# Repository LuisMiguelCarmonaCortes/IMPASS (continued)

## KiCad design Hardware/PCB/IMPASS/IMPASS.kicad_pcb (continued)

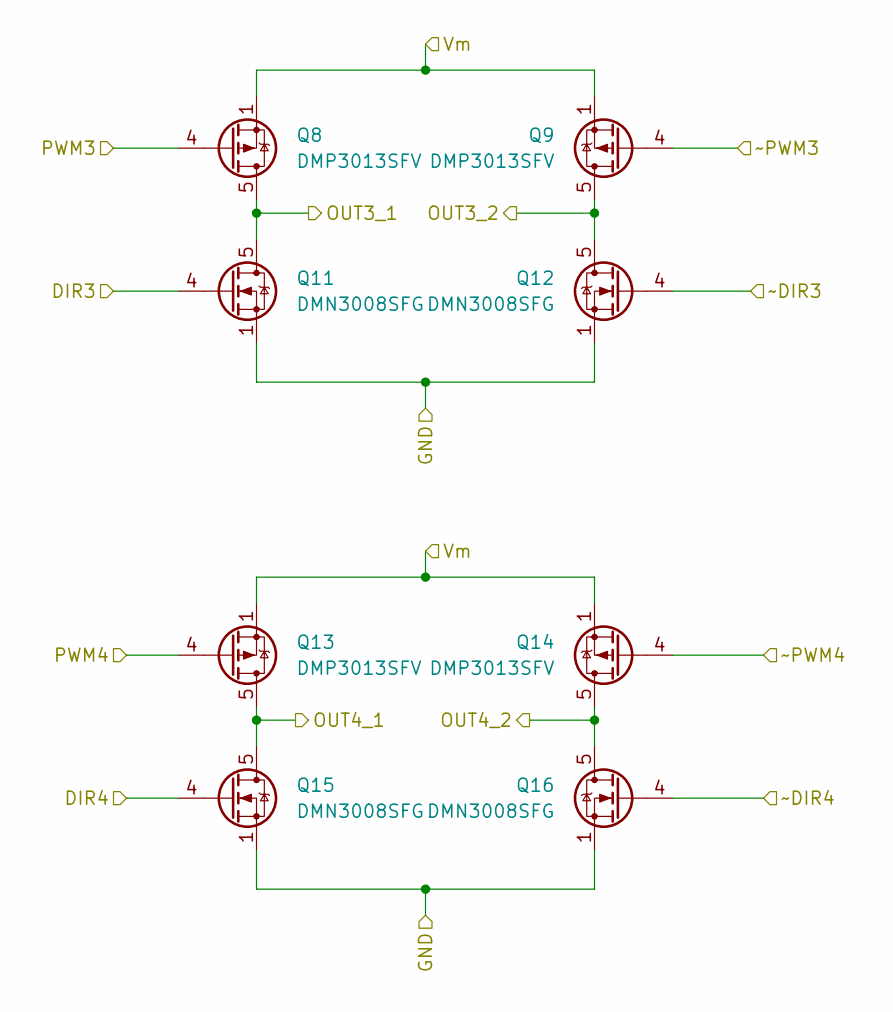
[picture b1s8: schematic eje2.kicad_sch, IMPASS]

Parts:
Q8, Q9, Q13, Q14: DMP3013SFV; Diodes_PowerDI3333-8
Q11, Q12, Q15, Q16: DMN3008SFG; Diodes_PowerDI3333-8

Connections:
12v: Q8.1 (S), Q8.2 (S), Q8.3 (S), Q9.1 (S), Q9.2 (S), Q9.3 (S), Q13.1 (S), Q13.2 (S), Q13.3 (S), Q14.1 (S), Q14.2 (S), Q14.3 (S); also elsewhere on the board
/Placa_potencia/Eje2/DIR3: Q11.4 (G); also elsewhere on the board
/Placa_potencia/Eje2/DIR4: Q15.4 (G); also elsewhere on the board
/Placa_potencia/Eje2/OUT3_1: Q8.5 (D), Q11.5 (D); also elsewhere on the board
/Placa_potencia/Eje2/OUT3_2: Q9.5 (D), Q12.5 (D); also elsewhere on the board
/Placa_potencia/Eje2/OUT4_1: Q13.5 (D), Q15.5 (D); also elsewhere on the board
/Placa_potencia/Eje2/OUT4_2: Q14.5 (D), Q16.5 (D); also elsewhere on the board
/Placa_potencia/Eje2/PWM3: Q8.4 (G); also elsewhere on the board
/Placa_potencia/Eje2/PWM4: Q13.4 (G); also elsewhere on the board
/Placa_potencia/Eje2/~DIR3: Q12.4 (G); also elsewhere on the board
/Placa_potencia/Eje2/~DIR4: Q16.4 (G); also elsewhere on the board
/Placa_potencia/Eje2/~PWM3: Q9.4 (G); also elsewhere on the board
/Placa_potencia/Eje2/~PWM4: Q14.4 (G); also elsewhere on the board
GND1: Q11.1 (S), Q11.2 (S), Q11.3 (S), Q12.1 (S), Q12.2 (S), Q12.3 (S), Q15.1 (S), Q15.2 (S), Q15.3 (S), Q16.1 (S), Q16.2 (S), Q16.3 (S); also elsewhere on the board

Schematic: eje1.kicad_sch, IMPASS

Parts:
Q2, Q3, Q4, Q6: DMP3013SFV; Diodes_PowerDI3333-8
Q71, Q73, Q75, Q77: DMN3008SFG; Diodes_PowerDI3333-8

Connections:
12v: Q2.1 (S), Q2.2 (S), Q2.3 (S), Q3.1 (S), Q3.2 (S), Q3.3 (S), Q4.1 (S), Q4.2 (S), Q4.3 (S), Q6.1 (S), Q6.2 (S), Q6.3 (S); also elsewhere on the board
/Placa_potencia/Eje1/DIR1: Q71.4 (G); also elsewhere on the board
/Placa_potencia/Eje1/DIR2: Q73.4 (G); also elsewhere on the board
/Placa_potencia/Eje1/OUT1_1: Q2.5 (D), Q71.5 (D); also elsewhere on the board
/Placa_potencia/Eje1/OUT1_2: Q3.5 (D), Q75.5 (D); also elsewhere on the board
/Placa_potencia/Eje1/OUT2_1: Q4.5 (D), Q73.5 (D); also elsewhere on the board
/Placa_potencia/Eje1/OUT2_2: Q6.5 (D), Q77.5 (D); also elsewhere on the board
/Placa_potencia/Eje1/PWM1: Q2.4 (G); also elsewhere on the board
/Placa_potencia/Eje1/PWM2: Q4.4 (G); also elsewhere on the board
/Placa_potencia/Eje1/~DIR1: Q75.4 (G); also elsewhere on the board
/Placa_potencia/Eje1/~DIR2: Q77.4 (G); also elsewhere on the board
/Placa_potencia/Eje1/~PWM1: Q3.4 (G); also elsewhere on the board
/Placa_potencia/Eje1/~PWM2: Q6.4 (G); also elsewhere on the board
GND1: Q71.1 (S), Q71.2 (S), Q71.3 (S), Q73.1 (S), Q73.2 (S), Q73.3 (S), Q75.1 (S), Q75.2 (S), Q75.3 (S), Q77.1 (S), Q77.2 (S), Q77.3 (S); also elsewhere on the board

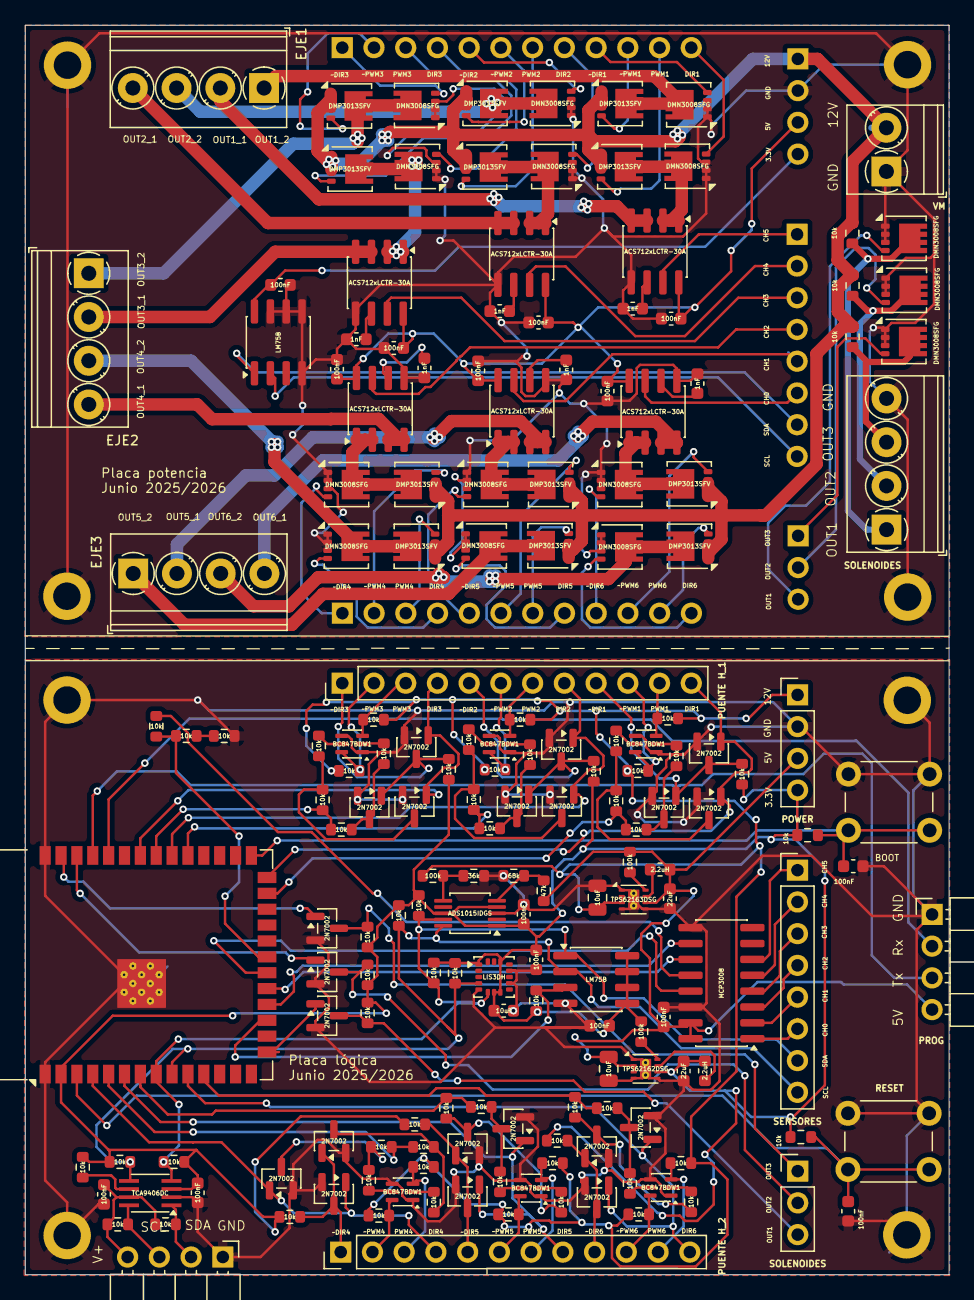
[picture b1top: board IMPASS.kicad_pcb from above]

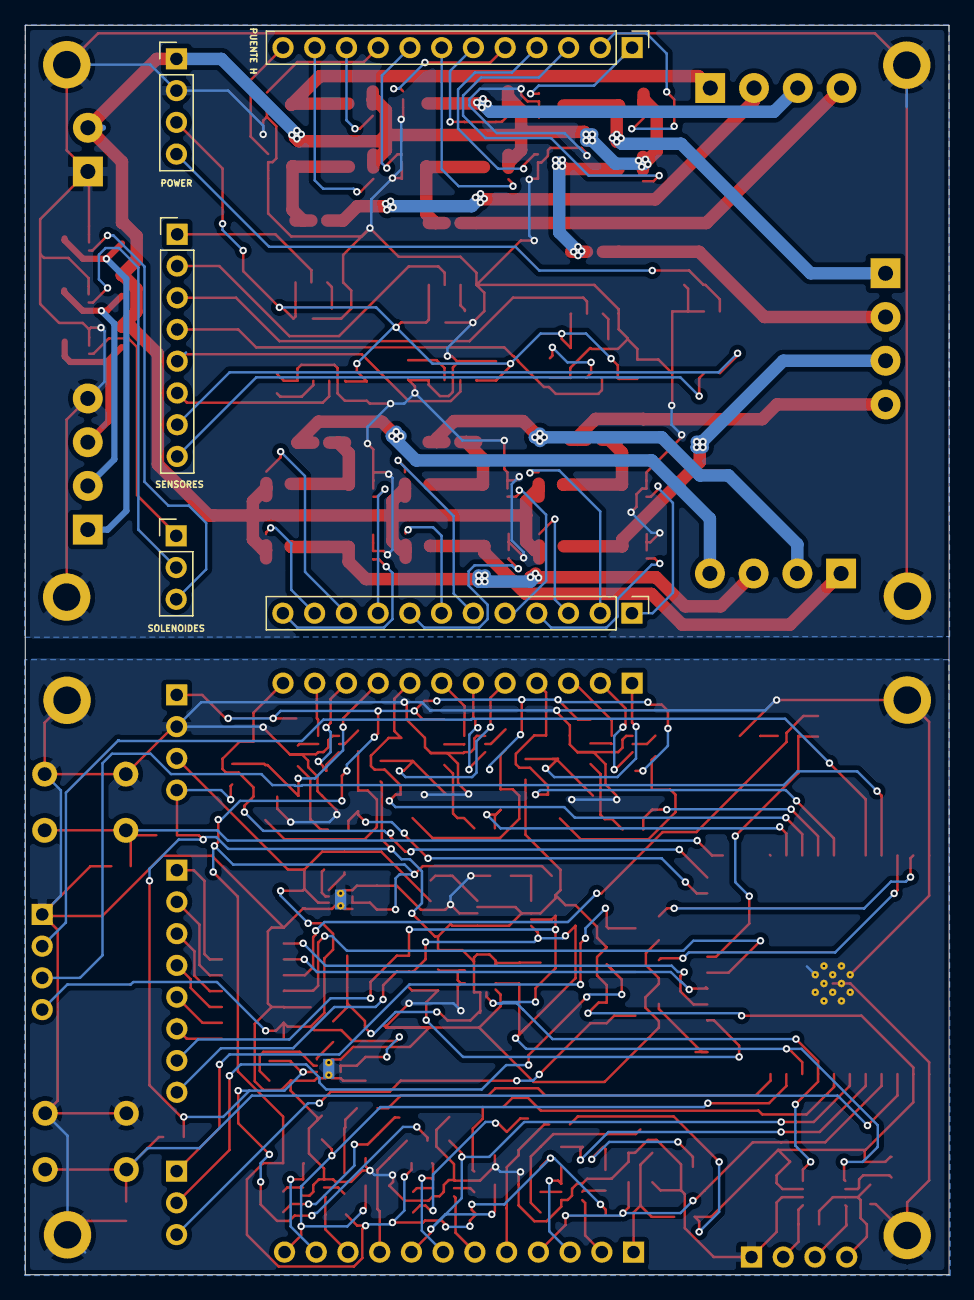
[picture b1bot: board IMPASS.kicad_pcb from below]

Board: 2 copper layers, 73.9 x 100.0 mm, 193 parts (5 on the bottom side), 159 nets.

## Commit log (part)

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2025-12-03 IMPASS schematics update
2025-12-03 Some change
2026-01-09 Schematics: Added mpu6050
2026-01-09 Update Datasheets
2026-01-11 Update to v1
2026-01-12 Update v1
2026-01-18 Removed
2026-03-23 Initial clean commit
2026-03-23 Añadir IMPASS como carpeta normal
2026-03-23 Repositorio Restored
2026-03-23 IMPASS: Tasks added - The creation of the tasks that are in the nucleo 0 - recibir_MQTT - manda_MQTT - The creation of the tasks that are in the nucleo 1 - vTaskTemperaturas - vTaskIntensidades - vTa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
2026-03-25 Restore all the documentation
2026-03-25 Restore all the schematics
2026-04-07 feat(mqtt): implement queue-based MQTT RX/TX handling
    Add FreeRTOS queues for MQTT communication, decoupling tasks from
    the MQTT client. Incoming messages are enqueued from the event handler,
    and outgoing messages are published via a dedicated TX task.
    Includes new mqtt_msg_t structure, system initialization updates,
    and improved mqtt.h documentation.
2026-06-08 Fix LM75 tests and I2C initialization issues
    - Fix undefined I2C initialization in LM75 unit tests
    - Move I2C initialization to proper app_main execution context
    - Ensure LM75 driver is correctly initialized before test execution
    - Fix test environment setup for ESP-IDF + Unity framework
    - Remove incorrect setUp-based initialization approach for hardware access
    - Resolve test failures caused by uninitialized I2C bus
2026-06-11 TFM-IMPASS: Added the topics of MQTT
2026-06-11 TFM-IMPASS: Created process_mqtt and updated mqtt
2026-06-11 TFM-IMPASS: Updated main.c - Now receibe MQTT msg - Now send MQTT msg
2026-06-11 TFM-IMPASS: Partition flash table
2026-06-16 Hardware: update schematic and PCB layout
2026-06-16 Hardware: update schematic and PCB layout - Replace the LDOs with buck converters - Replace AD5047D with LIS3DH
